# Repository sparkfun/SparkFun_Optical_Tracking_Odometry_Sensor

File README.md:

SparkFun Optical Tracking Odometry Sensor
========================================

![SparkFun Optical Tracking Odometry Sensor [SEN-24904]](docs/assets/img/otos-readme-banner.jpg)

[*SparkFun Optical Tracking Odometry Sensor [SEN-24904]*](https://www.sparkfun.com/products/24904)

The SparkFun Qwiic Optical Tracking Odometry Sensor empowers you to elevate your robot's navigation capabilities with exceptional precision and streamlined integration. This compact, all-in-one sensor leverages the power of the PAA5160E1 chip from PixArt Imaging Inc., delivering accurate dual-axis motion data across various hard floor surfaces. But that's not all! This sensor boasts a powerful built-in 6-axis Inertial Measurement Unit (IMU) and an onboard microcontroller that performs real-time sensor fusion and tracking algorithms.

Repository Contents
-------------------

* **/Hardware** - Eagle design files (.brd, .sch)
* **/Production** - Production panel files (.brd)

Documentation
--------------
* **[Arduino Library](https://github.com/sparkfun/SparkFun_Qwiic_OTOS_Arduino_Library)** - Arduino library for the SparkFun Optical Tracking Odometry Sensor.
* **[Hookup Guide](https://docs.sparkfun.com/SparkFun_Optical_Tracking_Odometry_Sensor/)** - Hookup guide for the SparkFun Optical Tracking Odometry Sensor.

License Information
-------------------

This product is _**open source**_! 

Please review the LICENSE.md file for license information. 

If you have any questions or concerns on licensing, please contact technical support on our [SparkFun forums](https://forum.sparkfun.com/viewforum.php?f=152).

Distributed as-is; no warranty is given.

- Your friends at SparkFun.

_<COLLABORATION CREDIT>_

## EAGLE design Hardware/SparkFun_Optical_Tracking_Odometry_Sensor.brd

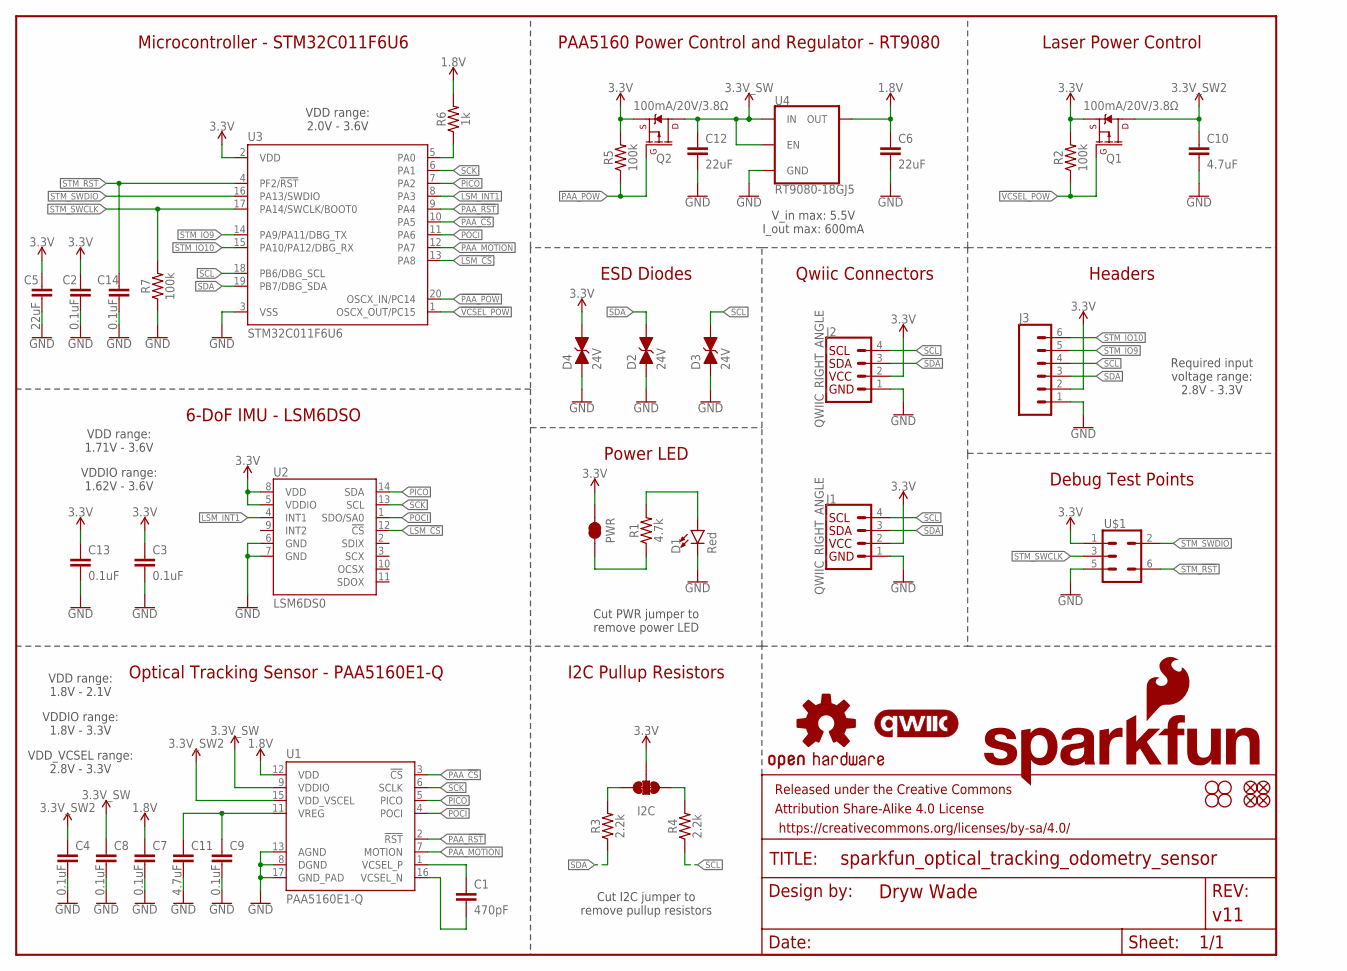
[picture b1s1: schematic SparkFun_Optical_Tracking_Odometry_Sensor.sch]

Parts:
C1: 470pF; 0603
C2, C3, C4, C7, C8, C9, C13, C14: 0.1uF; 0603
C5, C6, C12: 22uF; 0603
C10, C11: 4.7uF; 0603
D1: Red; LED-0603
D2, D3, D4: 24V; 0603
FD1, FD2, FD3, FD4: FIDUCIAL1X2; FIDUCIAL-1X2
FRAME1: FRAME-LETTER; CREATIVE_COMMONS
H1, H2, H3, H4: STAND-OFF
I2C: JUMPER-SMT_3_2-NC_TRACE_SILK; SMT-JUMPER_3_2-NC_TRACE_SILK
J1, J2: QWIIC_RIGHT_ANGLE; JST04_1MM_RA
J3: CONN_06NO_SILK_NO_POP; 1X06_NO_SILK
LOGO1: OSHW-LOGOS; OSHW-LOGO-S
LOGO2: QWIIC_LOGO_5MM; QWIIC_5MM
LOGO3: SFE_LOGO_NAME_FLAME.1_INCH; SFE_LOGO_NAME_FLAME_.1
PWR: JUMPER-SMT_2_NC_TRACE_SILK; SMT-JUMPER_2_NC_TRACE_SILK
Q1, Q2: 100mA/20V/3.8Ω; SOT-416FL
R1: 4.7k; 0603
R2, R5, R7: 100k; 0603
R3, R4: 2.2k; 0603
R6: 1k; 0603
U1: PAA5160E1-Q
U2: LSM6DS0; LGA14L
U3: STM32C011F6U6
U4: RT9080-18GJ5; SOT23-5
U$1: SWD-5PIN; PAD_05_03X2_TP_NO4

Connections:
1.8V: C6.1, C7.1, R6.2, U1.12 (VDD), U4.5 (OUT)
3.3V: C2.1, C3.1, C5.1, C13.1, D4.2 (C), I2C.2, J1.2, J2.2, J3.2, PWR.2, Q1.2 (S), Q2.2 (S), R2.2, R5.2, U2.5 (VDDIO), U2.8 (VDD), U3.2 (VDD), U$1.1
3.3V_SW: C8.1, C12.1, Q2.3 (D), U1.9 (VDDIO), U4.1 (IN), U4.3 (EN)
3.3V_SW2: C4.1, C10.1, Q1.3 (D), U1.15 (VDD_VSCEL)
!PAA_POW!: Q2.1 (G), R5.1, U3.20 (OSCX_IN/PC14)
!VCSEL_POW!: Q1.1 (G), R2.1, U3.1 (OSCX_OUT/PC15)
GND: C2.2, C3.2, C4.2, C5.2, C6.2, C7.2, C8.2, C9.2, C10.2, C11.2, C12.2, C13.2, C14.2, D1.C, D2.1 (A), D3.1 (A), D4.1 (A), J1.1, J2.1, J3.1, R7.1, U1.8 (DGND), U1.13 (AGND), U1.17 (GND_PAD), U2.6 (GND), U2.7 (GND), U3.3 (VSS), U4.2 (GND), U$1.5
LSM_!CS!: U2.12 (!CS!), U3.13 (PA8)
LSM_INT1: U2.4 (INT1), U3.8 (PA3)
unnamed: PWR.1, R1.1
unnamed: D1.A, R1.2
unnamed: C1.1, U1.1 (VCSEL_P)
unnamed: C1.2, U1.16 (VCSEL_N)
unnamed: I2C.3, R3.2
unnamed: I2C.1, R4.2
unnamed: C9.1, C11.1, U1.11 (VREG)
unnamed: R6.1, U3.5 (PA0)
PAA_!CS!: U1.3 (!CS!), U3.10 (PA5)
PAA_!RST!: U1.2 (!RST!), U3.9 (PA4)
PAA_MOTION: U1.7 (MOTION), U3.12 (PA7)
PICO: U1.5 (PICO), U2.14 (SDA), U3.7 (PA2)
POCI: U1.4 (POCI), U2.1 (SDO/SA0), U3.11 (PA6)
SCK: U1.6 (SCLK), U2.13 (SCL), U3.6 (PA1)
SCL: D3.2 (C), J1.4, J2.4, J3.4, R4.1, U3.18 (PB6/DBG_SCL)
SDA: D2.2 (C), J1.3, J2.3, J3.3, R3.1, U3.19 (PB7/DBG_SDA)
STM_!RST!: C14.1, U3.4 (PF2/!RST!), U$1.6
STM_IO9: J3.5, U3.14 (PA9/PA11/DBG_TX)
STM_IO10: J3.6, U3.15 (PA10/PA12/DBG_RX)
STM_SWCLK: R7.2, U3.17 (PA14/SWCLK/BOOT0), U$1.3
STM_SWDIO: U3.16 (PA13/SWDIO), U$1.2

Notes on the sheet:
Power LED
Optical Tracking Sensor - PAA5160E1-Q
6-DoF IMU - LSM6DSO
Microcontroller - STM32C011F6U6
PAA5160 Power Control and Regulator - RT9080
Debug Test Points
Qwiic Connectors
I2C Pullup Resistors
Cut I2C jumper to remove pullup resistors
Cut PWR jumper to remove power LED
Headers
ESD Diodes
Laser Power Control
V_in max: 5.5V I_out max: 600mA
VDD range: 2.0V - 3.6V
VDD range: 1.71V - 3.6V
VDDIO range: 1.62V - 3.6V
VDD range: 1.8V - 2.1V
VDDIO range: 1.8V - 3.3V
VDD_VCSEL range: 2.8V - 3.3V
Required input voltage range: 2.8V - 3.3V

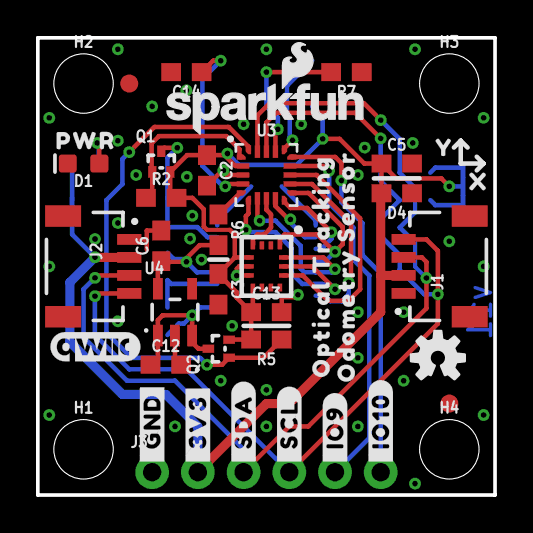
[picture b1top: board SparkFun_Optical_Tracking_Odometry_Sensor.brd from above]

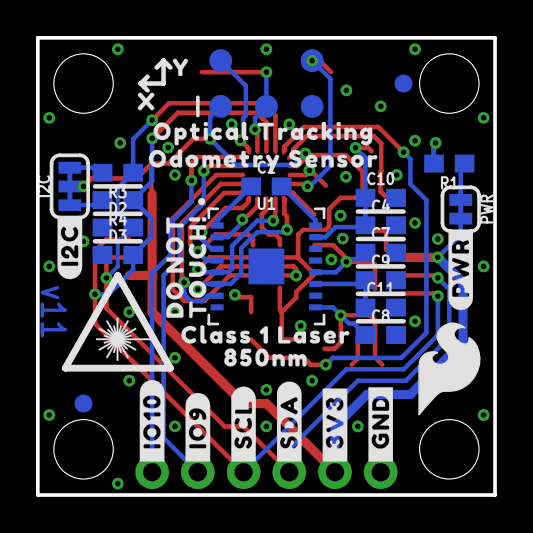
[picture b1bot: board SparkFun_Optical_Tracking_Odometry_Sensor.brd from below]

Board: 2 copper layers, 25.4 x 25.4 mm, 78 parts (35 on the bottom side), 30 nets.

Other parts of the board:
U$2, U$8: #_GND#0
U$3, U$9: #_3V3#0
U$4, U$10: #_SDA#0
U$5, U$11: #_SCL#0
U$6: CLASS_1_LASER0
U$7, U$23: #_IO10#0
U$12, U$32: #_IO9#0
U$14, U$16: OPTICAL_TRACKING0
U$15, U$17: ODOMETRY_SENSOR0
U$18, U$30: X0
U$20: #PWR#0
U$21: TOUCH##0
U$22: DO_NOT0
U$24: SFE_LOGO_FLAME_.2
U$25: PWR0
U$26: #I2C#0
U$27: ORDERING_INSTRUCTIONS
U$28: 850NM0
U$29, U$31: Y0

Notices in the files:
parts and their libraries:
SparkFun-Aesthetics: Licensing: Creative Commons ShareAlike 4.0 International - https://creativecommons.org/licenses/by-sa/4.0
SparkFun-Aesthetics: Released under the Creative Commons Attribution Share-Alike 4.0 License
SparkFun-Aesthetics: https://creativecommons.org/licenses/by-sa/4.0
